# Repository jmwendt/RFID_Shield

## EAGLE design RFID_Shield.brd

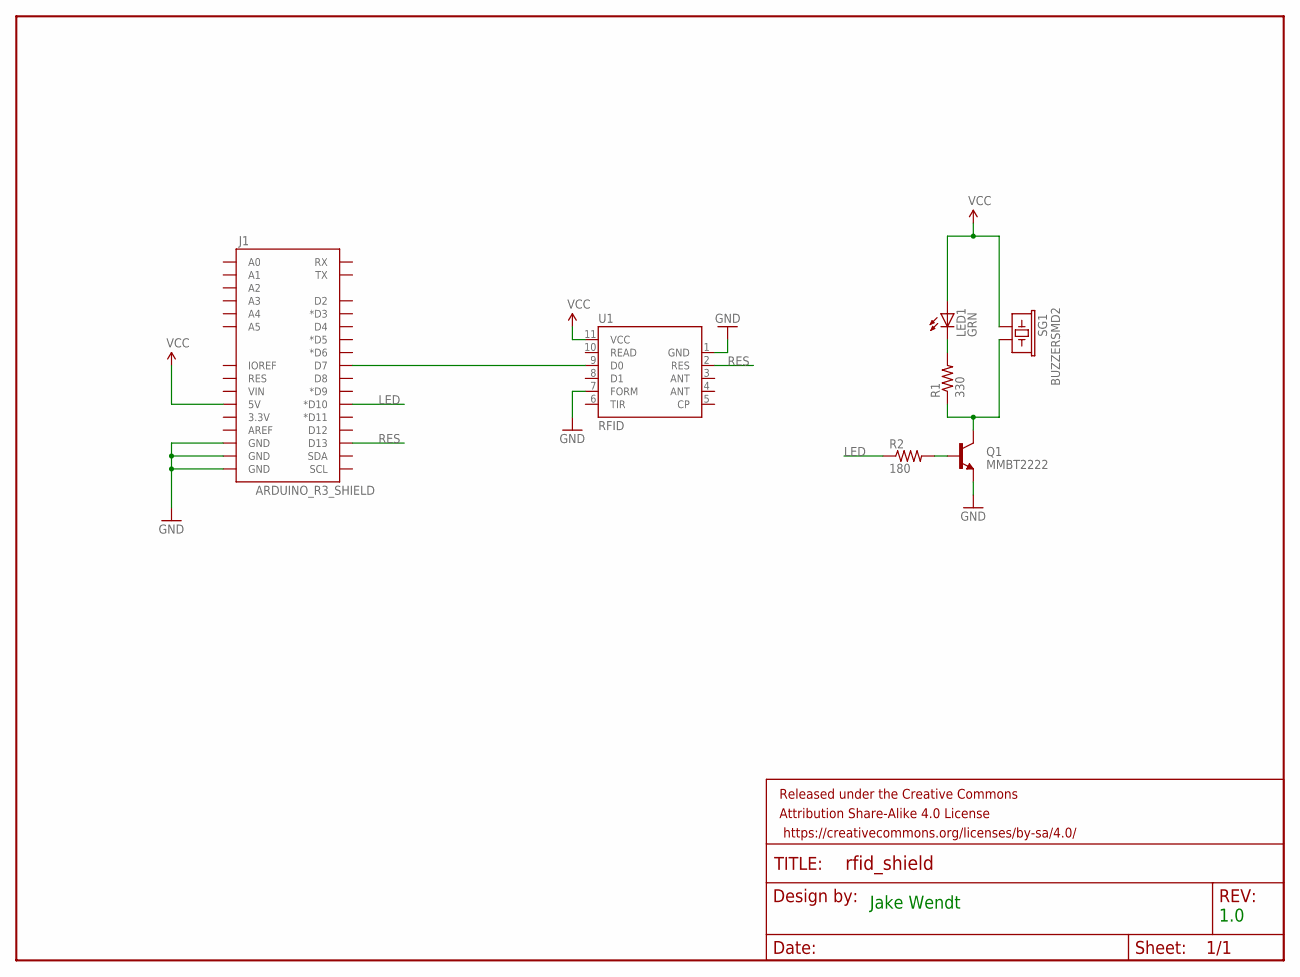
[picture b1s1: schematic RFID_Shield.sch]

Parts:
FRAME1: FRAME-LETTER; CREATIVE_COMMONS
J1: ARDUINO_R3_SHIELD; UNO_R3_SHIELD
LED1: GRN; LED-0603
Q1: MMBT2222; SOT23-3
R1: 330; 0402-RES
R2: 180; 0402-RES
SG1: BUZZERSMD2; BUZZER-CCV
U1: RFID; ID_PACKAGE

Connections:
GND: J1.GND@0 (GND), J1.GND@1 (GND), J1.GND@2 (GND), Q1.2 (E), U1.1 (GND), U1.7 (FORM)
LED: J1.D10 (*D10), R2.1
unnamed: Q1.3 (C), R1.1, SG1.- (2)
unnamed: J1.D7, U1.9 (D0)
unnamed: LED1.C, R1.2
unnamed: Q1.1 (B), R2.2
RES: J1.D13, U1.2 (RES)
VCC: J1.5V, LED1.A, SG1.+ (1), U1.11 (VCC)

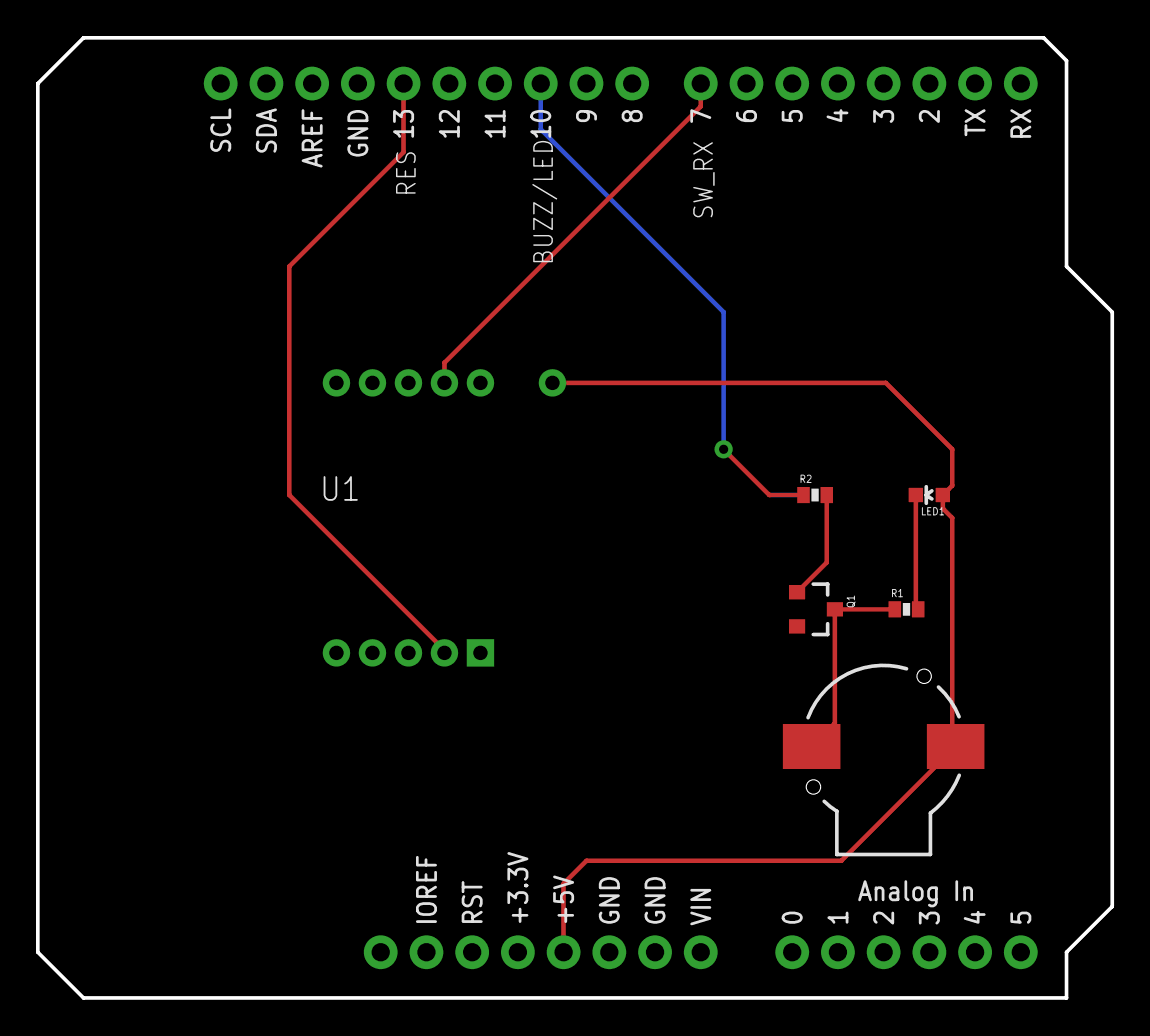
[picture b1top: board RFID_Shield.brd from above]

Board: 2 copper layers, 59.7 x 53.3 mm, 8 parts (0 on the bottom side), 8 nets.

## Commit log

2016-06-10 Added silk screen for pins used.
2016-06-19 Fixed missing VCC and GND connections.

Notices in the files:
parts and their libraries:
SparkFun-Aesthetics: Licensing: Creative Commons ShareAlike 4.0 International - https://creativecommons.org/licenses/by-sa/4.0
SparkFun-Aesthetics: Released under the Creative Commons Attribution Share-Alike 4.0 License
SparkFun-Aesthetics: https://creativecommons.org/licenses/by-sa/4.0
